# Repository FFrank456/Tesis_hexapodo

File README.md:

# Tesis — Sistema robótico cooperativo bioinspirado (dos hexápodos)

UTEC · Ingeniería Mecatrónica · Asesor: prof. Dante Inga Narváez
Equipo: Alfredo Erazo Yalopalin, Aleskyjubinsl Alcarraz Jaime, Flavio Alarcón Muñoz

Dos hexápodos que cooperan para **mapear y detectar gases tóxicos** en terrenos irregulares o peligrosos: minas y socavones, zonas de desastre y laboratorios.

| Unidad | Resumen |
|---|---|
| **U1**, líder | 18× MG996R, Pololu Mini Maestro 18, Raspberry Pi 5, Orbbec Gemini 2, RTAB-Map + Nav2, LiPo 3S |
| **U2**, modular | 18 micromotores Pololu HPCB 12 V 100:1 (formato N20), 6× MOD_DRV (ESP32 + 3× DRV8876) en **bus CAN** hacia una maestra ESP32-S3, respaldo Wi-Fi/ESP-NOW, batería de ~14,4 V (4S), placas de alimentación PCBicho v1.3 |

## Estructura (bóveda de Obsidian)

| Carpeta | Contenido |
|---|---|
| `01-mecanica/` | Notas de diseño, CAD (STL/3MF), paquetes URDF, soportes |
| `02-electronica/` | Arquitectura, MOD_DRV (Altium), PCBicho 6× MP1584 (KiCad), diagramas |
| `03-control/` | Control de corriente/velocidad/posición (firmware `ControlCurrentN20`, ESP-IDF), calibración de servos |
| `04-navegacion/` | RTAB-Map + Nav2 (U1) |
| `05-documentacion/` | Tesis y capítulos, estado del arte, gases, cooperación, normativa, decisiones |

Abrir la carpeta como bóveda en Obsidian. Cada área tiene una nota índice con el mismo nombre que la carpeta.

## Qué no está en este repositorio (ver `.gitignore`)
- Mallas de los URDF, `base_link.stl` y archivos STEP: se regeneran desde Fusion 360 o Altium. Las piezas STL/3MF pequeñas sí se versionan.
- Historial, vistas previas y logs de Altium; historial de KiCad.
- Repositorios independientes:
  - `02-electronica/unidad2-PCB-pata-v1` → Altium 365
- PDF de referencias (en `05-documentacion/referencias/`, solo en local).

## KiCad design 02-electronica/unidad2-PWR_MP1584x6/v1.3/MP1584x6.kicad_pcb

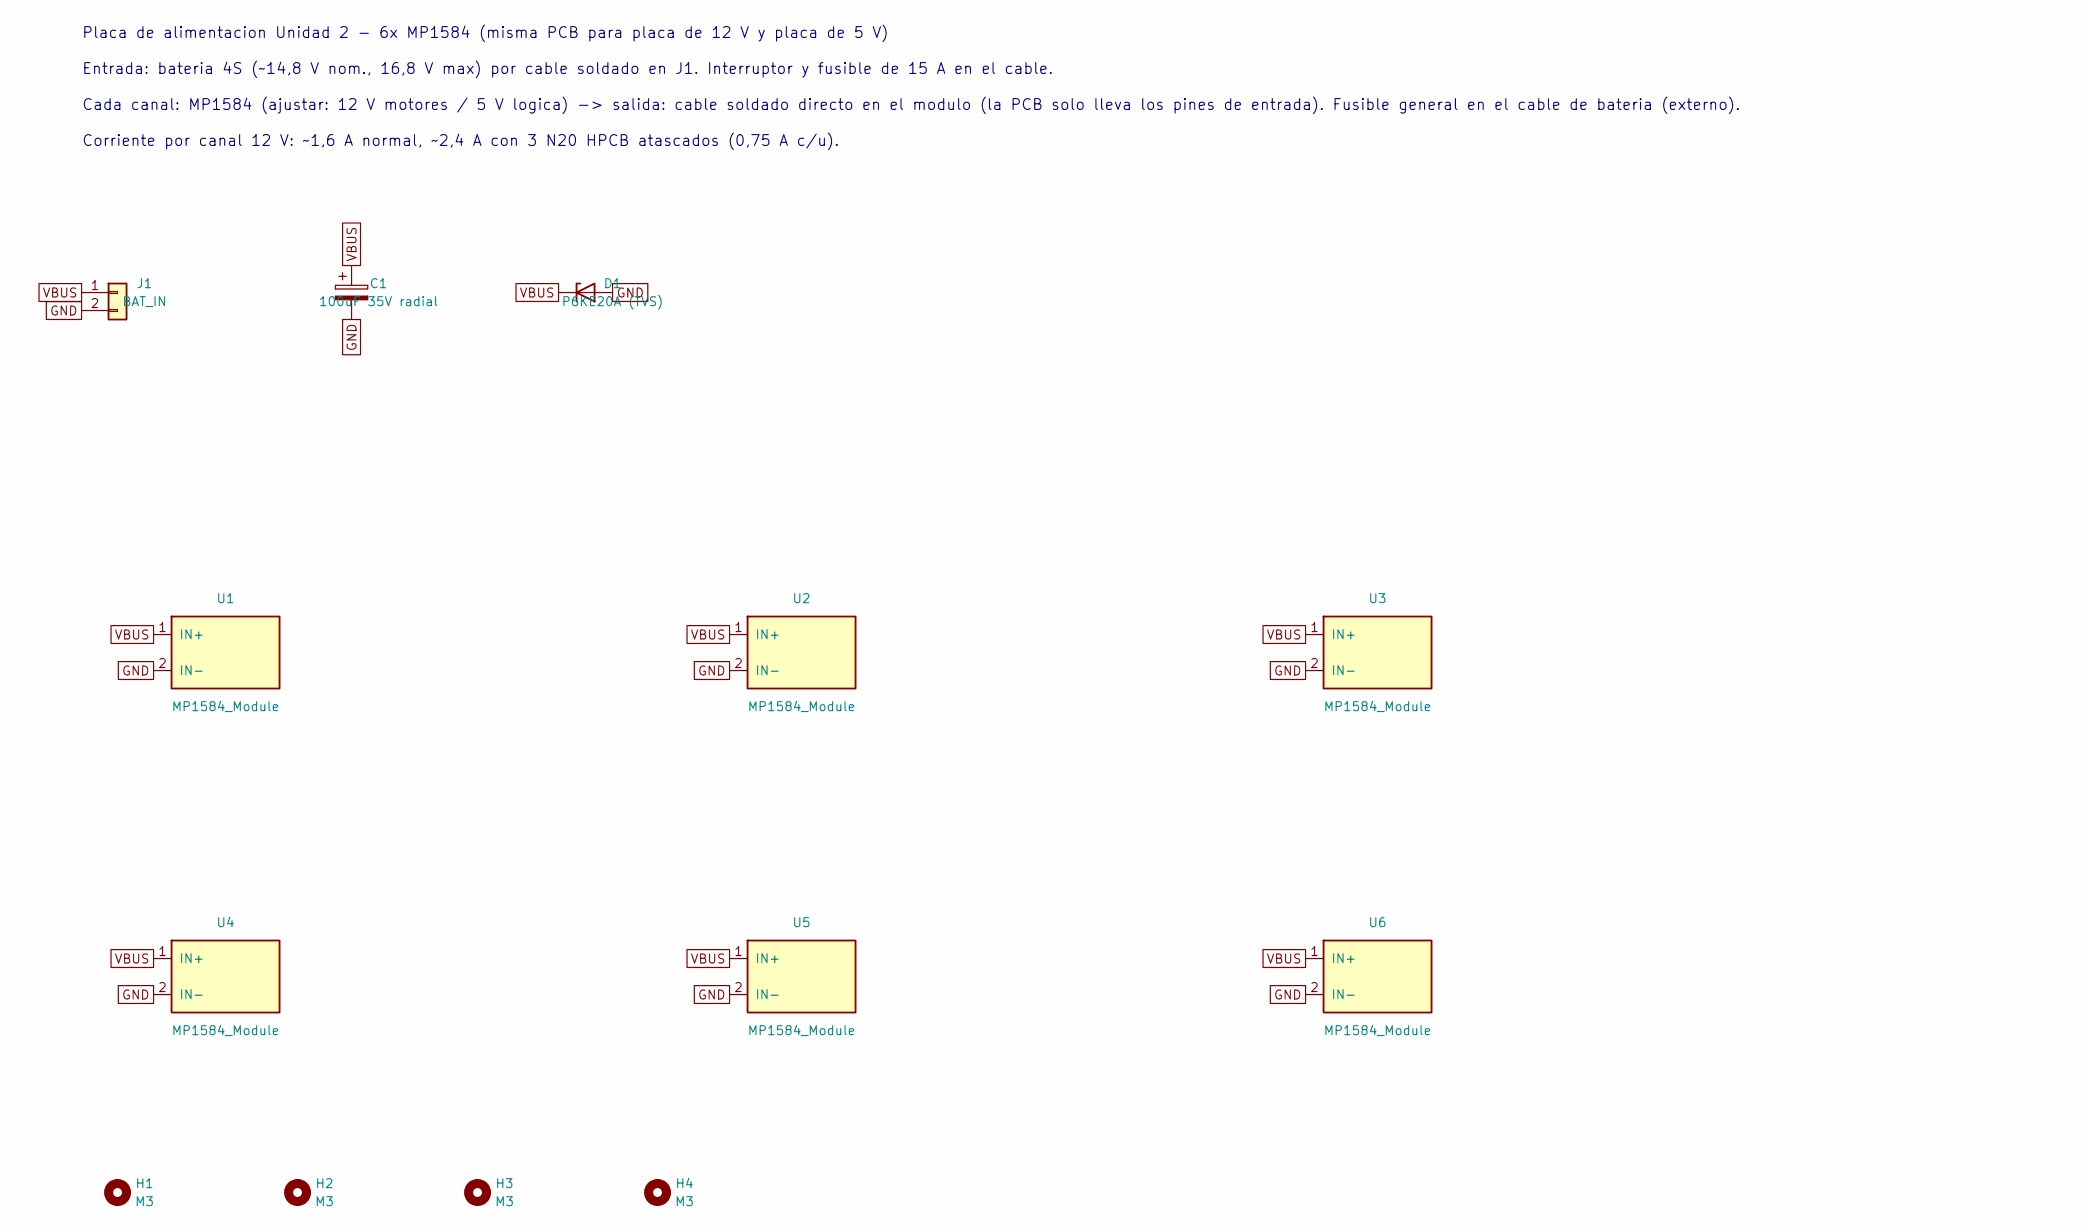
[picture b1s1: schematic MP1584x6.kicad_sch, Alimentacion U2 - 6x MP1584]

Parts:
C1: 100uF 35V radial; CP_Radial_D6.3mm_P2.50mm
D1: P6KE20A (TVS); D_DO-15_P3.81mm_Vertical_KathodeUp
H1, H2, H3, H4: M3; MountingHole_3.2mm_M3
J1: BAT_IN; SolderWire-2sqmm_1x02_P7.8mm_D2mm_OD3.9mm
U1, U2, U3, U4, U5, U6: MP1584_Module; MP1584_Module_22x17mm_IN

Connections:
GND: C1.2, D1.2 (A), J1.2, U1.2 (IN-), U2.2 (IN-), U3.2 (IN-), U4.2 (IN-), U5.2 (IN-), U6.2 (IN-)
VBUS: C1.1, D1.1 (K), J1.1, U1.1 (IN+), U2.1 (IN+), U3.1 (IN+), U4.1 (IN+), U5.1 (IN+), U6.1 (IN+)

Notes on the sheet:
Placa de alimentacion Unidad 2 - 6x MP1584 (misma PCB para placa de 12 V y placa de 5 V)
Entrada: bateria 4S (~14,8 V nom., 16,8 V max) por cable soldado en J1. Interruptor y fusible de 15 A en el cable.
Cada canal: MP1584 (ajustar: 12 V motores / 5 V logica) -> salida: cable soldado directo en el modulo (la PCB solo lleva los pines de entrada). Fusible general en el cable de bateria (externo).
Corriente por canal 12 V: ~1,6 A normal, ~2,4 A con 3 N20 HPCB atascados (0,75 A c/u).

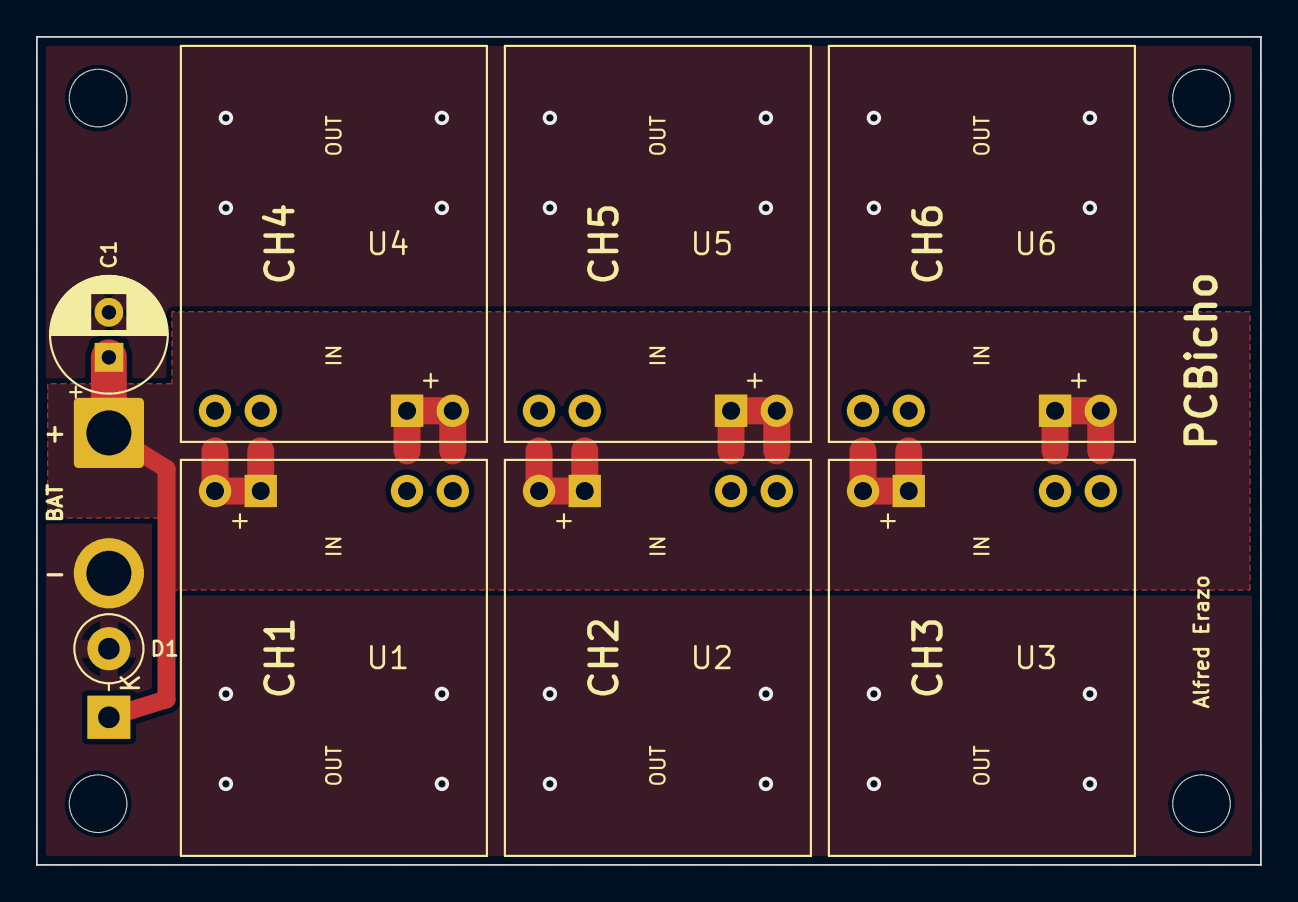
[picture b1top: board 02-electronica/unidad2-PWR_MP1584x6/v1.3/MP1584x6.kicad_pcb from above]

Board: 2 copper layers, 68.0 x 46.0 mm, 13 parts (0 on the bottom side), 2 nets.

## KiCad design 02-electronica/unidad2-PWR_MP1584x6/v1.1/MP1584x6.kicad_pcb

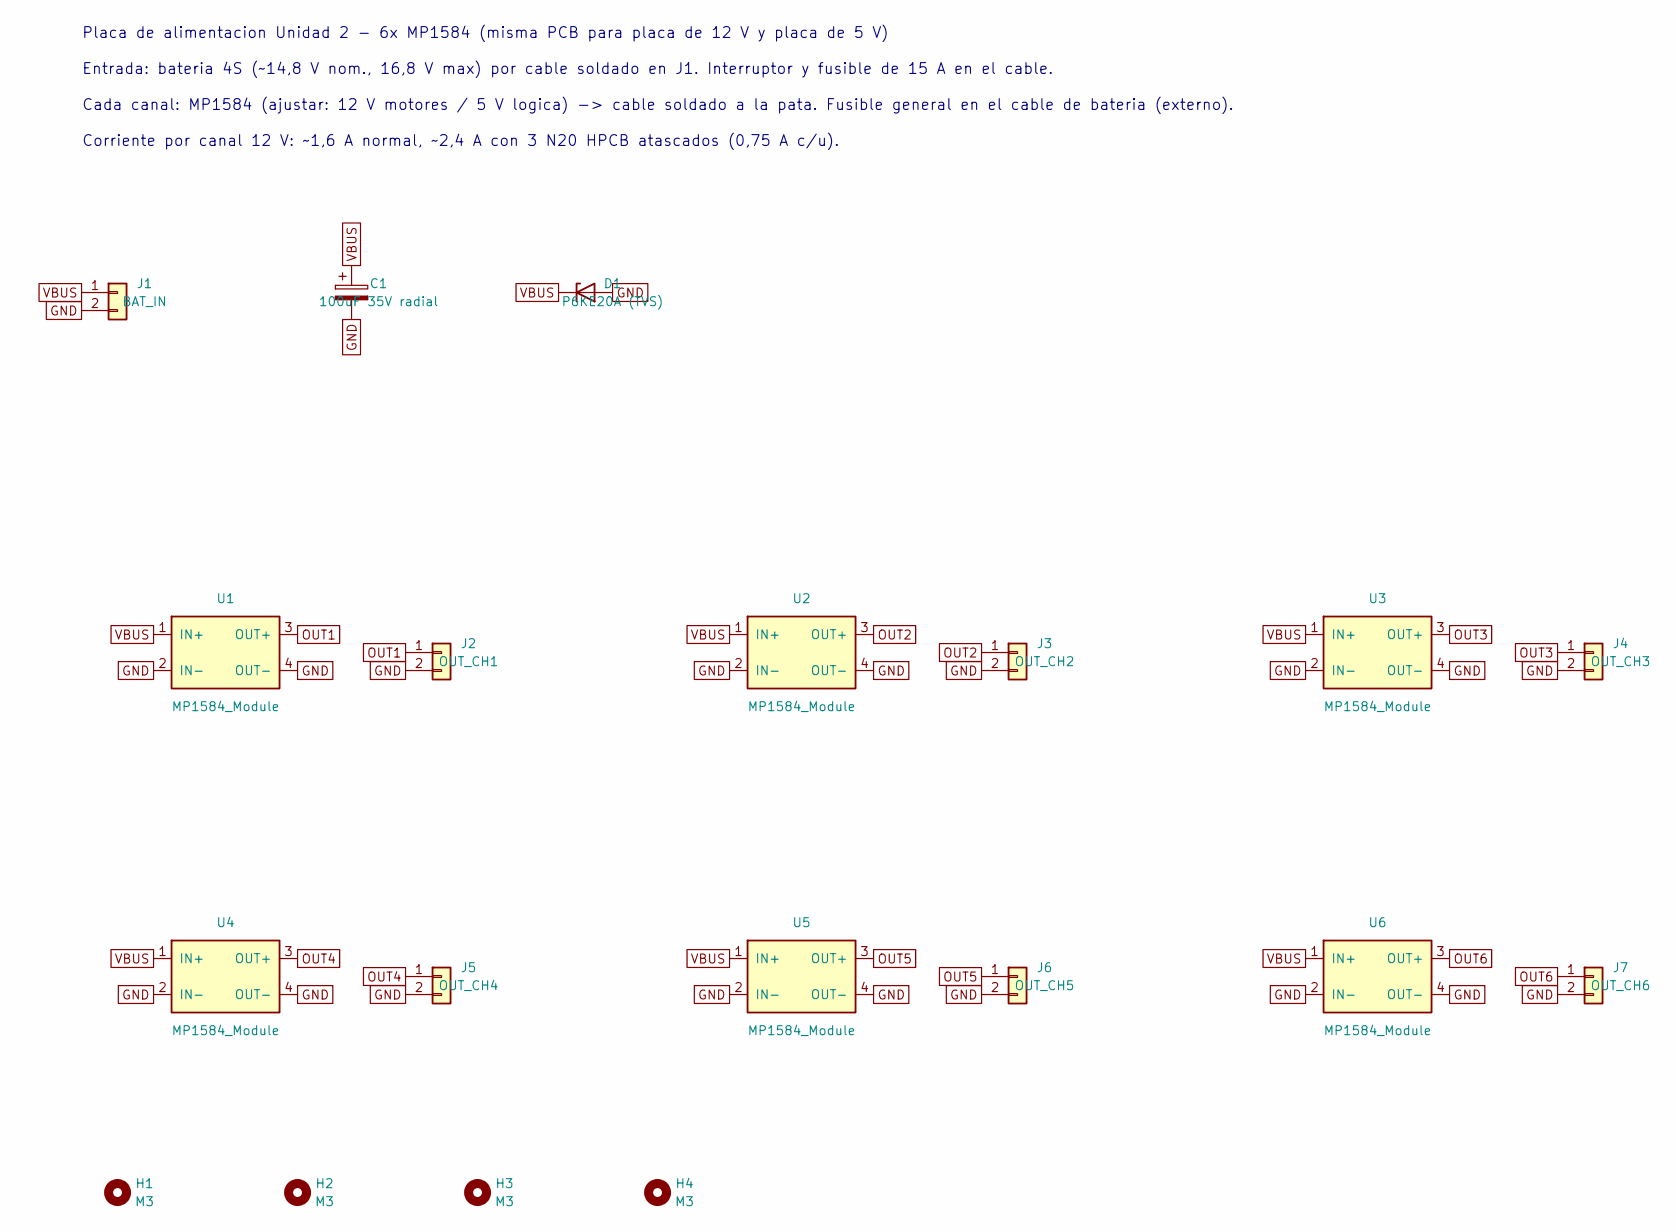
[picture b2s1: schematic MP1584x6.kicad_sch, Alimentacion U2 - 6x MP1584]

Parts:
C1: 100uF 35V radial; CP_Radial_D6.3mm_P2.50mm
D1: P6KE20A (TVS); D_DO-15_P3.81mm_Vertical_KathodeUp
H1, H2, H3, H4: M3; MountingHole_3.2mm_M3
J1: BAT_IN; SolderWire-2sqmm_1x02_P7.8mm_D2mm_OD3.9mm
J2: OUT_CH1; SolderWire-1sqmm_1x02_P5.4mm_D1.4mm_OD2.7mm
J3: OUT_CH2; SolderWire-1sqmm_1x02_P5.4mm_D1.4mm_OD2.7mm
J4: OUT_CH3; SolderWire-1sqmm_1x02_P5.4mm_D1.4mm_OD2.7mm
J5: OUT_CH4; SolderWire-1sqmm_1x02_P5.4mm_D1.4mm_OD2.7mm
J6: OUT_CH5; SolderWire-1sqmm_1x02_P5.4mm_D1.4mm_OD2.7mm
J7: OUT_CH6; SolderWire-1sqmm_1x02_P5.4mm_D1.4mm_OD2.7mm
U1, U2, U3, U4, U5, U6: MP1584_Module; MP1584_Module_22x17mm

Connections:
GND: C1.2, D1.2 (A), J1.2, J2.2, J3.2, J4.2, J5.2, J6.2, J7.2, U1.2 (IN-), U1.4 (OUT-), U2.2 (IN-), U2.4 (OUT-), U3.2 (IN-), U3.4 (OUT-), U4.2 (IN-), U4.4 (OUT-), U5.2 (IN-), U5.4 (OUT-), U6.2 (IN-), U6.4 (OUT-)
OUT1: J2.1, U1.3 (OUT+)
OUT2: J3.1, U2.3 (OUT+)
OUT3: J4.1, U3.3 (OUT+)
OUT4: J5.1, U4.3 (OUT+)
OUT5: J6.1, U5.3 (OUT+)
OUT6: J7.1, U6.3 (OUT+)
VBUS: C1.1, D1.1 (K), J1.1, U1.1 (IN+), U2.1 (IN+), U3.1 (IN+), U4.1 (IN+), U5.1 (IN+), U6.1 (IN+)

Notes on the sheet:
Placa de alimentacion Unidad 2 - 6x MP1584 (misma PCB para placa de 12 V y placa de 5 V)
Entrada: bateria 4S (~14,8 V nom., 16,8 V max) por cable soldado en J1. Interruptor y fusible de 15 A en el cable.
Cada canal: MP1584 (ajustar: 12 V motores / 5 V logica) -> cable soldado a la pata. Fusible general en el cable de bateria (externo).
Corriente por canal 12 V: ~1,6 A normal, ~2,4 A con 3 N20 HPCB atascados (0,75 A c/u).

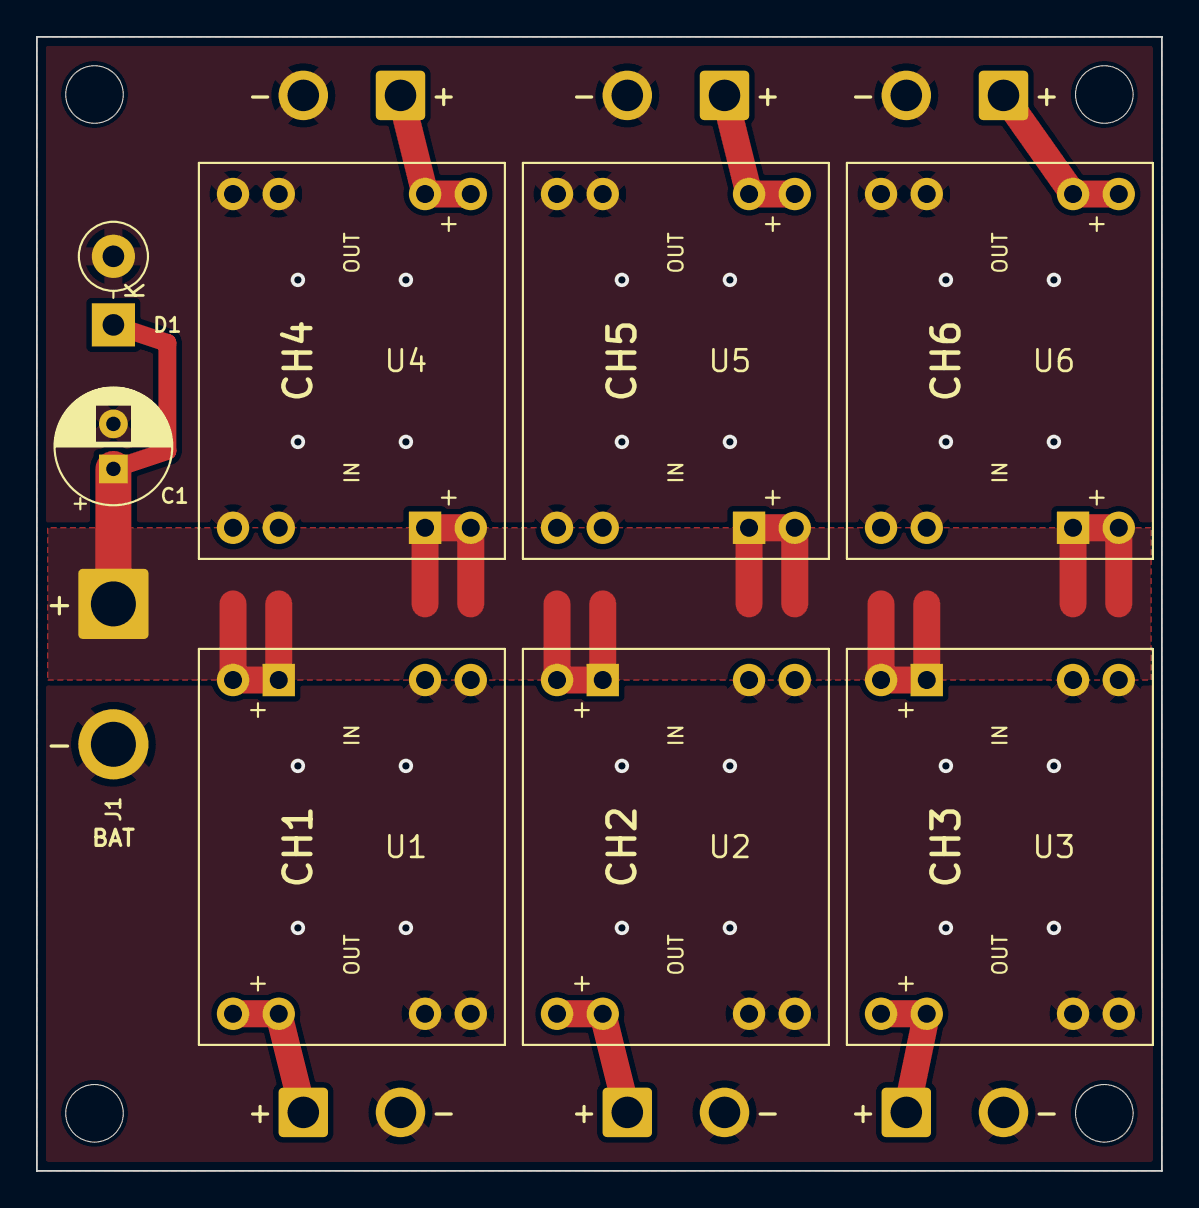
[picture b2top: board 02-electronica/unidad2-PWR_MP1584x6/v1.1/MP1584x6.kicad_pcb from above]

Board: 2 copper layers, 62.5 x 63.0 mm, 19 parts (0 on the bottom side), 8 nets.
